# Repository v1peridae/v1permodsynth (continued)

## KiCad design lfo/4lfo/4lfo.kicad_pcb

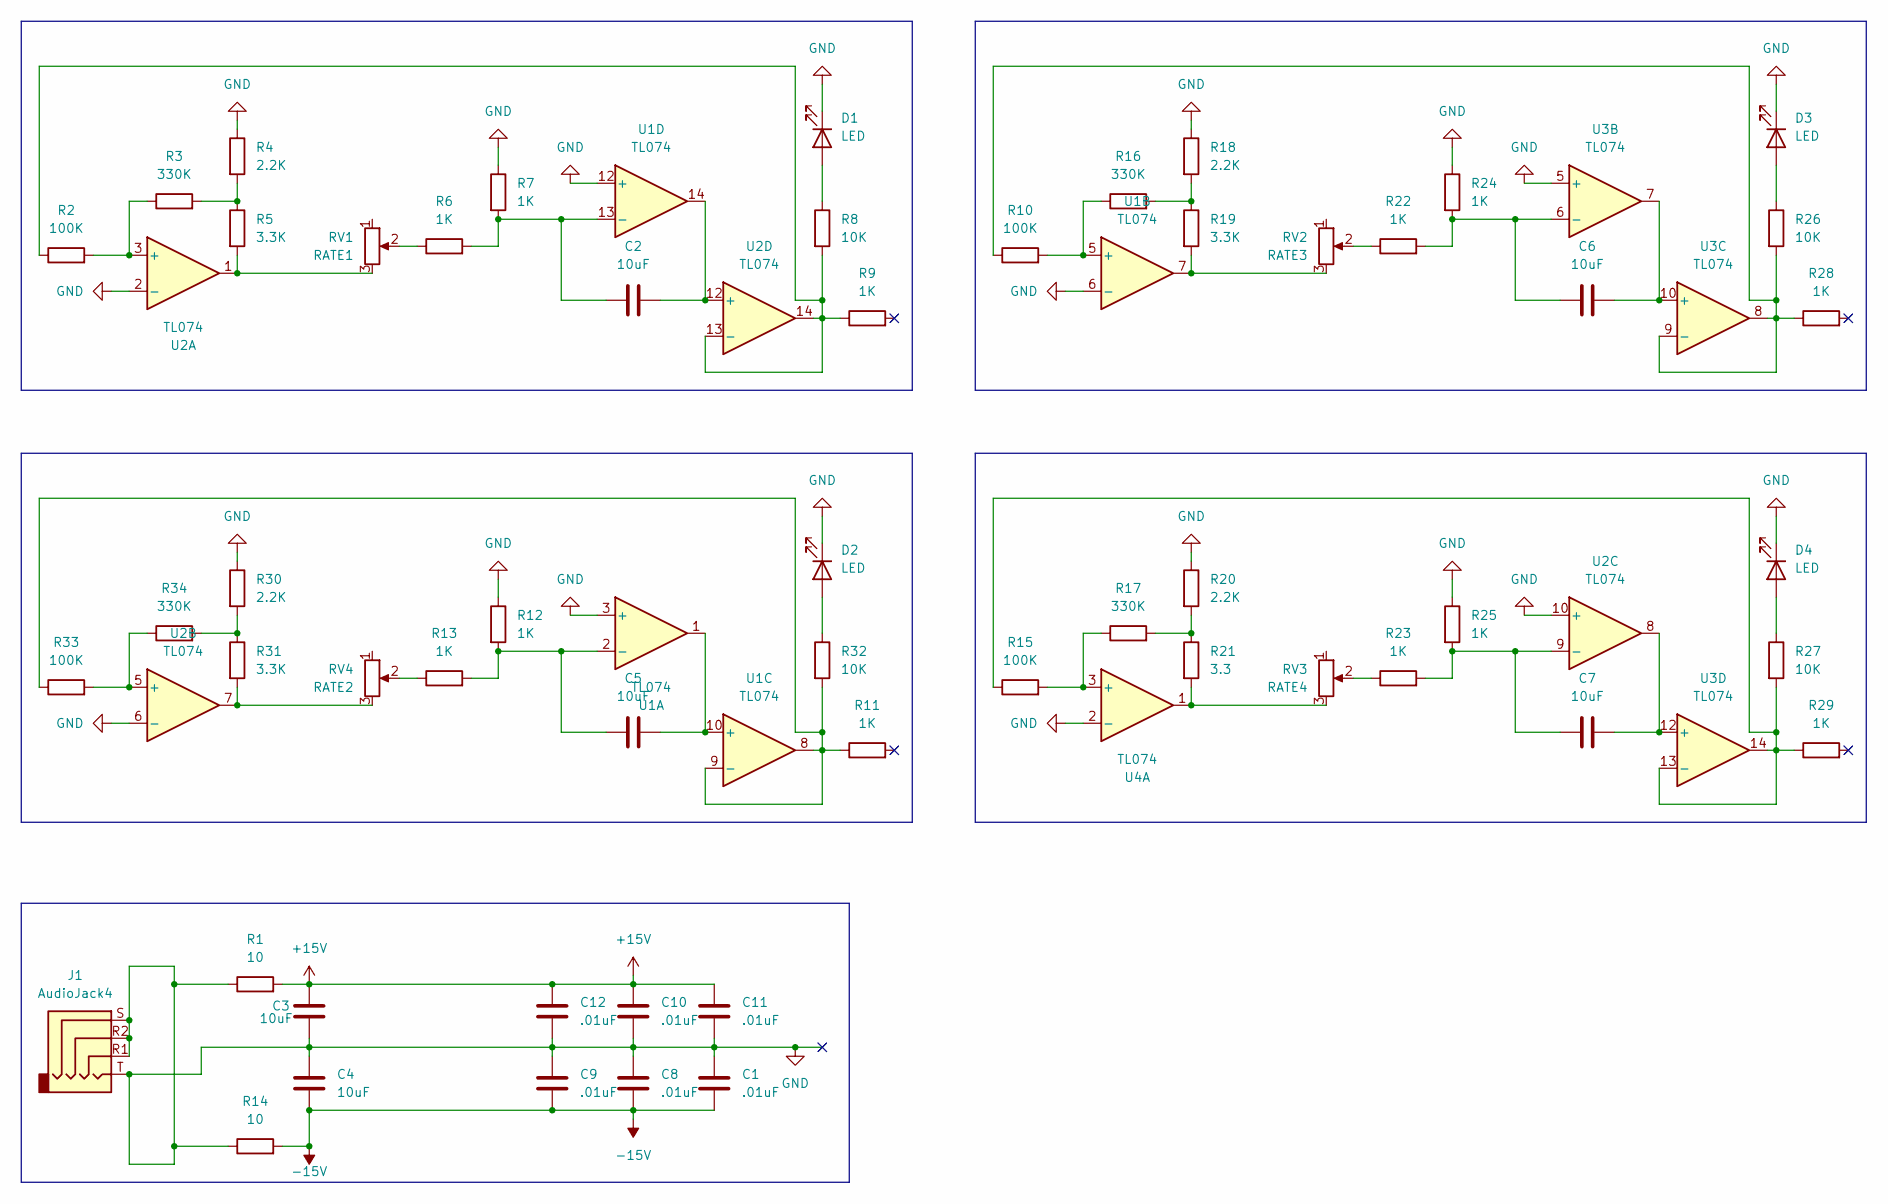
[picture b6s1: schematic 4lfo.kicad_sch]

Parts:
C1, C8, C9, C10, C11, C12: .01uF; C_0805_2012Metric
C2, C3, C4, C5, C6, C7: 10uF; C_1206_3216Metric
D1, D2, D3, D4: LED; LED_1206_3216Metric
J1: AudioJack4; Jack_3.5mm_QingPu_WQP-PJ398SM_Vertical_CircularHoles
R1, R14: 10; R_0805_2012Metric
R2, R10, R15, R33: 100K; R_0805_2012Metric
R3, R16, R17, R34: 330K; R_0805_2012Metric
R4, R18, R20, R30: 2.2K; R_0805_2012Metric
R5, R19, R31: 3.3K; R_0805_2012Metric
R6, R7, R9, R11, R12, R13, R22, R23, R24, R25, R28, R29: 1K; R_0805_2012Metric
R8, R26, R27, R32: 10K; R_0805_2012Metric
R21: 3.3; R_0805_2012Metric
RV1: RATE1; SOIC-14_3.9x8.7mm_P1.27mm
RV2: RATE3; SOIC-14_3.9x8.7mm_P1.27mm
RV3: RATE4; SOIC-14_3.9x8.7mm_P1.27mm
RV4: RATE2; SOIC-14_3.9x8.7mm_P1.27mm
U1, U2, U3, U4: TL074; SOIC-14_3.9x8.7mm_P1.27mm

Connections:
+15V: C3.2, C10.1, C11.1, C12.1, R1.2
-15V: C1.2, C4.2, C8.2, C9.2, R14.2
GND: C1.1, C3.1, C4.1, C8.1, C9.1, C10.2, C11.2, C12.2, D1.1 (K), D2.1 (K), D3.1 (K), D4.1 (K), J1.R1, J1.R2, J1.S, J1.T, R1.1, R4.1, R7.1, R12.1, R14.1, R18.1, R20.1, R24.1, R25.1, R30.1, U1.3 (+), U1.6 (-), U1.12 (+), U2.2 (-), U2.6 (-), U2.10 (+), U3.5 (+), U4.2 (-)
unnamed: D1.2 (A), R8.1
unnamed: D2.2 (A), R32.1
unnamed: D3.2 (A), R26.1
unnamed: D4.2 (A), R27.1
unnamed: R3.2, R4.2, R5.1
unnamed: R5.2, RV1.3, U2.1
unnamed: R6.1, RV1.2
unnamed: R13.1, RV4.2
unnamed: R16.2, R18.2, R19.1
unnamed: R17.2, R20.2, R21.1
unnamed: R19.2, RV2.3, U1.7
unnamed: R21.2, RV3.3, U4.1
unnamed: R22.1, RV2.2
unnamed: R23.1, RV3.2
unnamed: R30.2, R31.1, R34.2
unnamed: R31.2, RV4.3, U2.7
unnamed: C5.1, R12.2, R13.2, U1.2 (-)
unnamed: R10.2, R16.1, U1.5 (+)
unnamed: C5.2, U1.1, U1.10 (+)
unnamed: R11.1, R32.2, R33.1, U1.8, U1.9 (-)
unnamed: C2.1, R6.2, R7.2, U1.13 (-)
unnamed: R2.2, R3.1, U2.3 (+)
unnamed: R33.2, R34.1, U2.5 (+)
unnamed: C7.1, R23.2, R25.2, U2.9 (-)
unnamed: C2.2, U1.14, U2.12 (+)
unnamed: R2.1, R8.2, R9.1, U2.13 (-), U2.14
unnamed: C6.1, R22.2, R24.2, U3.6 (-)
unnamed: C6.2, U3.7, U3.10 (+)
unnamed: R10.1, R26.2, R28.1, U3.8, U3.9 (-)
unnamed: C7.2, U2.8, U3.12 (+)
unnamed: R15.1, R27.2, R29.1, U3.13 (-), U3.14
unnamed: R15.2, R17.1, U4.3 (+)

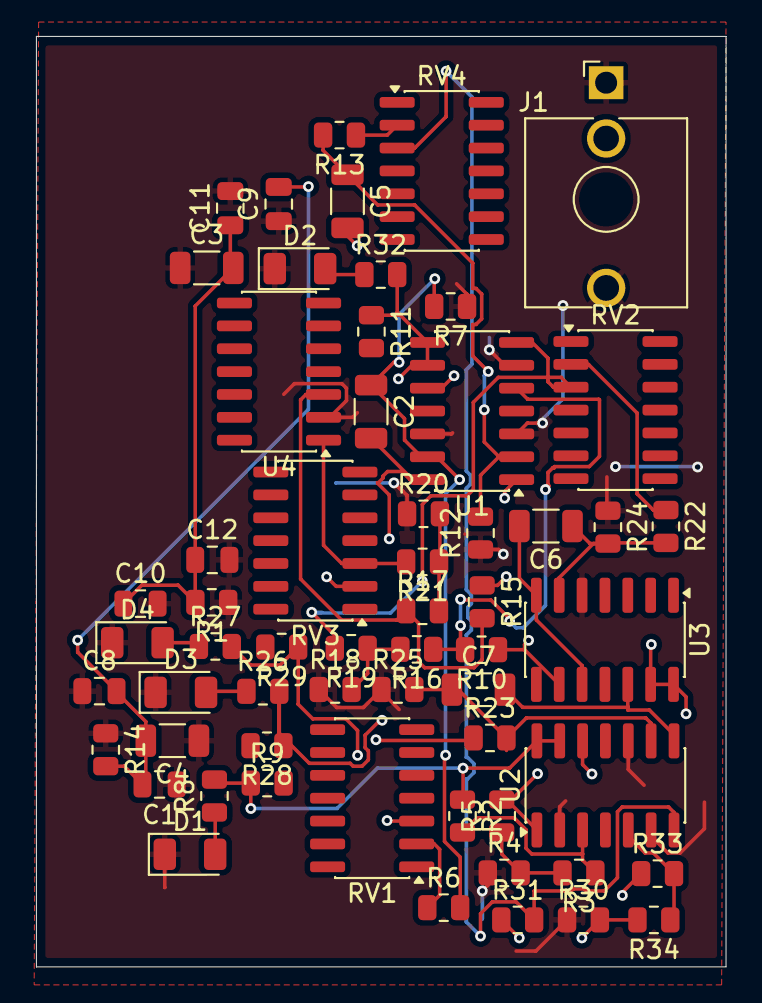
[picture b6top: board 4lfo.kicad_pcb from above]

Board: 4 copper layers, 38.3 x 51.7 mm, 59 parts (0 on the bottom side), 35 nets.

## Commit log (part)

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2026-01-30 adding the pcb
2026-01-30 mostly getting started i will add more stuff tmrw
2026-03-20 add details
2026-03-20 change letter
2026-03-31 better indepth readme
2026-05-21 added other components imma add
2026-05-29 finished the mod synth :D
    (i keep on forgetting to commit :sob:)
2026-06-09 COMMITTING SUM STUFF!
